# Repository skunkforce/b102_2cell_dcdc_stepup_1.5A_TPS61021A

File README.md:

# edgy_board number b102
This design is part of the [edgy board project](https://github.com/skunkforce/edgy_boards). It provides a 1.2A step up from 2 battery cells.

# getting started
This repository uses submodules. After cloning use the command 

```$ git submodule update --init --recursive```

to pull the submodules before opening the project with kicad. 

# Tests
Tests can be found in [TESTS.md](TESTS.md)

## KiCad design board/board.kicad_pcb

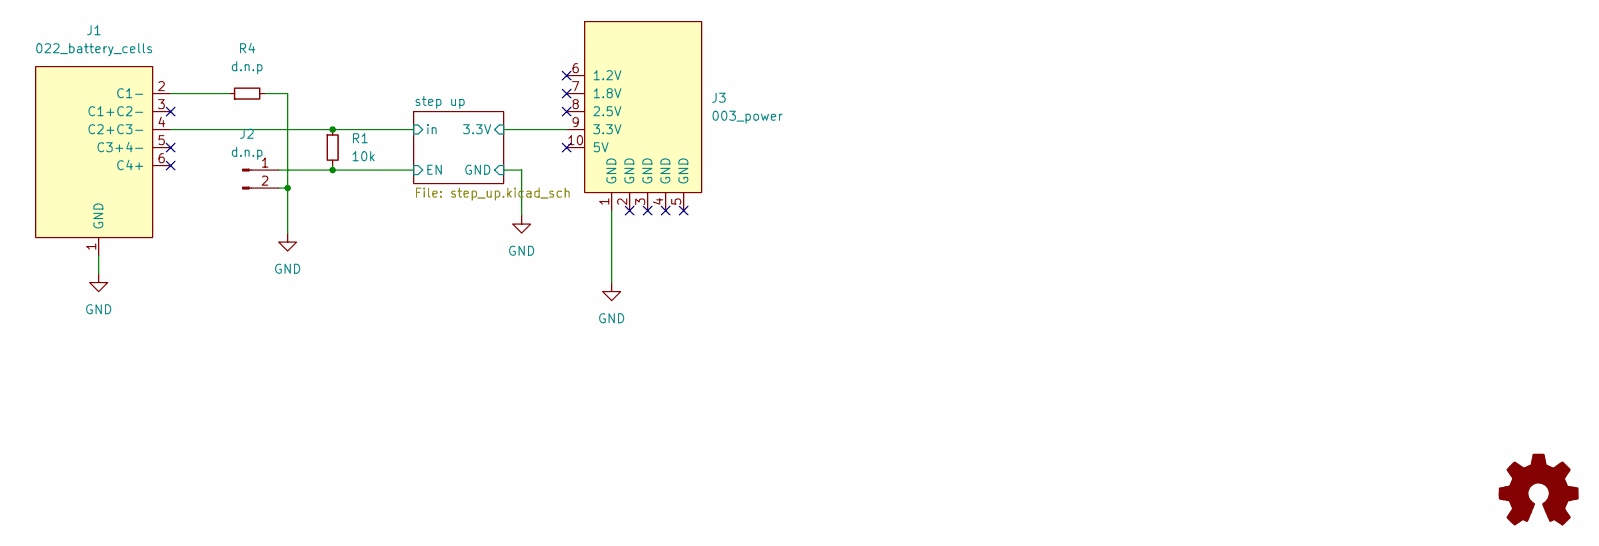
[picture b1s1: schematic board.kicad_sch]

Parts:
J1: 022_battery_cells; on_edge_2x05_device
J2: d.n.p; PinHeader_1x02_P2.54mm_Vertical
J3: 003_power; on_edge_2x05_host
LOGO1: Logo_Open_Hardware_Small; OSHW-Symbol_6.7x6mm_SilkScreen
R1: 10k; R_0603_1608Metric
R4: d.n.p; R_0603_1608Metric

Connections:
/step up/3.3V: J3.9 (3.3V); also elsewhere on the board
/step up/EN: J2.1, R1.2; also elsewhere on the board
/step up/in: J1.4 (C2+C3-), R1.1; also elsewhere on the board
GND: J1.1 (GND), J2.2, J3.1 (GND), R4.2; also elsewhere on the board
unnamed: J1.2 (C1-), R4.1

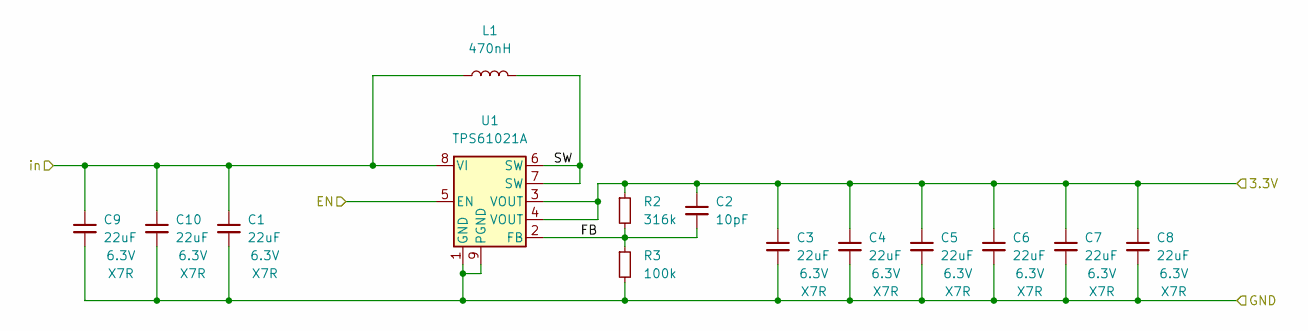
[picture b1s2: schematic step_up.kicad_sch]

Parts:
C1, C3, C4, C5, C6, C7, C8, C9, C10: 22uF; C_1206_3216Metric; Voltage 6.3V
C2: 10pF; C_0603_1608Metric
L1: 470nH; 744383360047; MPN 744383360047; DigiKey_PN 732-5691-1-ND
R2: 316k; R_0603_1608Metric
R3: 100k; R_0603_1608Metric
U1: TPS61021A; WSON-8-1EP_2x2mm_P0.5mm_EP0.9x1.6mm; MPN TPS61021ADSGR; Digi-Key_PN 296-TPS61021ADSGRCT-ND

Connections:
/step up/3.3V: C2.1, C3.1, C4.1, C5.1, C6.1, C7.1, C8.1, R2.1, U1.3 (VOUT), U1.4 (VOUT); also elsewhere on the board
/step up/EN: U1.5 (EN); also elsewhere on the board
/step up/FB: C2.2, R2.2, R3.1, U1.2 (FB)
/step up/SW: L1.2, U1.6 (SW), U1.7 (SW)
/step up/in: C1.1, C9.1, C10.1, L1.1, U1.8 (VI); also elsewhere on the board
GND: C1.2, C3.2, C4.2, C5.2, C6.2, C7.2, C8.2, C9.2, C10.2, R3.2, U1.1 (GND), U1.9 (PGND); also elsewhere on the board

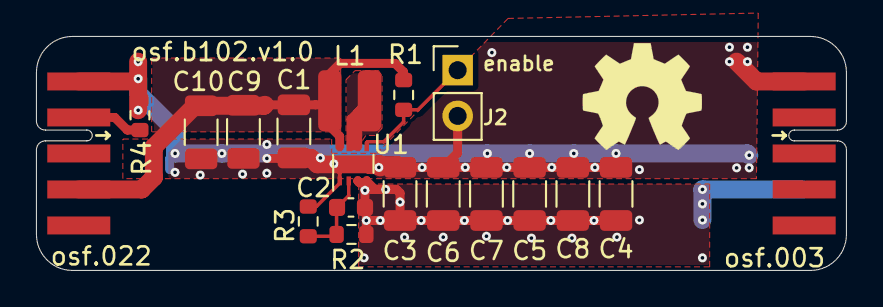
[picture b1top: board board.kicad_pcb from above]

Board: 2 copper layers, 45.0 x 13.0 mm, 20 parts (0 on the bottom side), 7 nets.

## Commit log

2023-03-04 initial
2023-03-08 corrected U1 part number
2023-06-04 added resistor to allow shorting of bat low to gnd
2023-06-05 added decoupling caps
